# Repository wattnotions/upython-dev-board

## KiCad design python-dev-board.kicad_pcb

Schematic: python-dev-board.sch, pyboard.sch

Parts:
BOOT1: SW_Push; Switches_Push_Switch_506-FSMSM
C1, C2, C3, C4: 12p; C_0603
C5, C6: 2u2; C_0603
C7, C8: 1u; C_0603
C9, C10, C11, C12, C13, C15: 100n; C_0603
C14: 4u7; C_0603
IC1: STM32F405RGT; LQFP64
J3: USB_OTG; USB_Micro-B_Molex-105017-0001
LED1: WS2812B
NRST1: SW_Push; Switches_Push_Switch_506-FSMSM
R2: 1k; R_0603
R3: 10M; R_0603
R4, R5, R6: 100k; R_0603
R7, R8: 15R; R_0603
R9, R10: 4.7k; R_0603
R11, R12: 10K; R_0603
SW1: SW_Push; Switches_Push_Switch_506-FSMSM
Y1: 8MHz; QC5CA8_8mhz_oscillator
Y2: 32.768KHz; ABS06-32.768KHZ_smd_crystal

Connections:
+3V3: BOOT1.2, C8.1, C9.1, C10.1, C11.1, C12.1, C13.1, C14.1, IC1.1 (VBAT), IC1.2 (PC13), IC1.13 (VDDA), IC1.19 (VDD), IC1.32 (VDD), IC1.48 (VDD), IC1.64 (VDD), LED1.1 (VCC), R9.1, R10.1, R11.1; also elsewhere on the board
+BATT: C7.1; also elsewhere on the board
/BOOT0: BOOT1.1, IC1.60 (BOOT0), R4.1
/FS_DM: IC1.44 (PA11), R8.1
/FS_DP: IC1.45 (PA12), R7.1
/FS_USB_ID: IC1.43 (PA10), J3.4 (ID)
/FS_VUSB: IC1.42 (PA9), J3.1 (VBUS)
/GPS_HSD_SW: IC1.9 (PC1)
/GPS_I2C_SCK: IC1.58 (PB6), R10.2
/GPS_I2C_SDA: IC1.59 (PB7), R9.2
/GPS_TX: IC1.30 (PB11), R5.1
/GSM_HSD_SW: IC1.10 (PC2)
/GSM_PWRKEY: IC1.8 (PC0)
/GSM_RX: IC1.29 (PB10)
/INA219_HSD_SW: IC1.26 (PB0)
/INST1_HSD_SW: IC1.25 (PC5)
/INST1_TTL_RX: IC1.14 (PA0)
/INST1_TTL_TX: IC1.15 (PA1)
/INST2_HSD_SW: IC1.24 (PC4)
/INST2_TTL_RX: IC1.16 (PA2)
/INST2_TTL_TX: IC1.17 (PA3)
/INST3_HSD_SW: IC1.11 (PC3)
/INST3_TTL_RX: IC1.37 (PC6)
/INST3_TTL_TX: IC1.38 (PC7)
/IO_PA4: IC1.20 (PA4)
/IO_PA5: IC1.21 (PA5)
/IO_PA6: IC1.22 (PA6)
/IO_PA7: IC1.23 (PA7), LED1.4 (DIN)
/IO_PA14: IC1.49 (PA14)
/IO_PA15: IC1.50 (PA15)
/IO_PB1: IC1.27 (PB1)
/IO_PB2: IC1.28 (PB2), R2.1
/IO_PB3: IC1.55 (PB3)
/IO_PB4: IC1.56 (PB4)
/IO_PB9: IC1.62 (PB9)
/IO_PB12: IC1.33 (PB12)
/IO_PB13: IC1.34 (PB13)
/IO_PB14: IC1.35 (PB14)
/IO_PB15: IC1.36 (PB15)
/LEDR1: IC1.41 (PA8)
/MMA_AVDD: IC1.57 (PB5), R6.1
/N$1: C5.2, IC1.47 (VCAP_2)
/N$2: C6.2, IC1.31 (VCAP_1)
/N$5: C4.1, IC1.3 (PC14), Y2.2
/N$6: C3.1, IC1.4 (PC15), Y2.1
/N$9: C1.1, IC1.6 (PH1), Y1.1
/N$10: C2.1, IC1.5 (PH0), Y1.2
/NRST: C15.1, IC1.7 (NRST), NRST1.2, R11.2
/SDIO_CK: IC1.53 (PC12)
/SDIO_CMD: IC1.54 (PD2)
/SDIO_D0: IC1.39 (PC8)
/SDIO_D1: IC1.40 (PC9)
/SDIO_D2: IC1.51 (PC10)
/SDIO_D3: IC1.52 (PC11), R3.1
/SD_CARD_HSD_SW: IC1.61 (PB8)
/USR_SW: IC1.46 (PA13), R12.2
GND: C1.2, C2.2, C3.2, C4.2, C5.1, C6.1, C7.2, C8.2, C9.2, C10.2, C11.2, C12.2, C13.2, C14.2, C15.2, IC1.12 (VSSA), IC1.18 (VSS), IC1.63 (VSS), J3.5 (GND), LED1.3 (GND), NRST1.1, R2.2, R3.2, R4.2, R5.2, R6.2, SW1.1; also elsewhere on the board
unnamed: J3.2 (D-), R8.2
unnamed: J3.3 (D+), R7.2
unnamed: R12.1, SW1.2

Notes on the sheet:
DFU boot
TX(4)
RX(4)
TX(2)
RX(2)
TX(6)
RX(6)
I2C(1) - SCL
I2C(1) - SDA
TX(3)
RX(3)

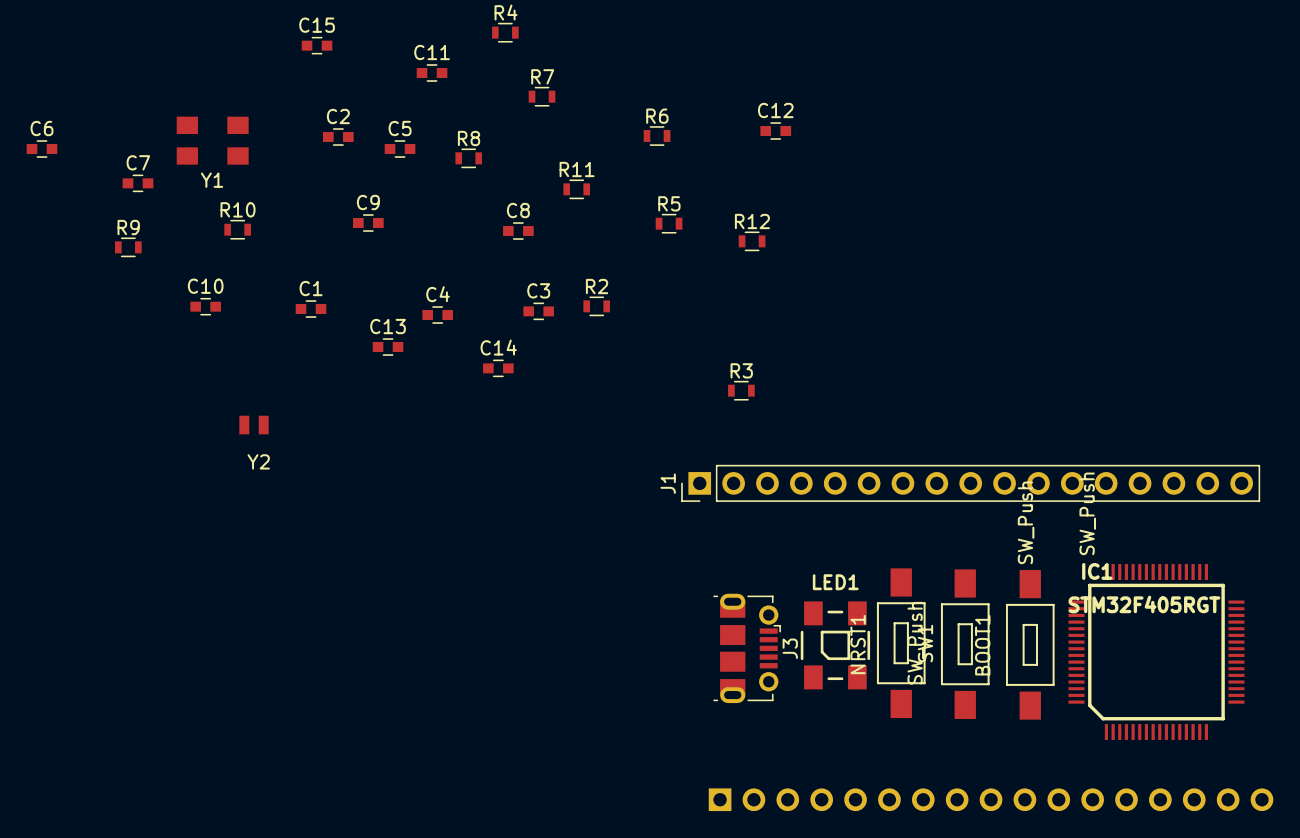
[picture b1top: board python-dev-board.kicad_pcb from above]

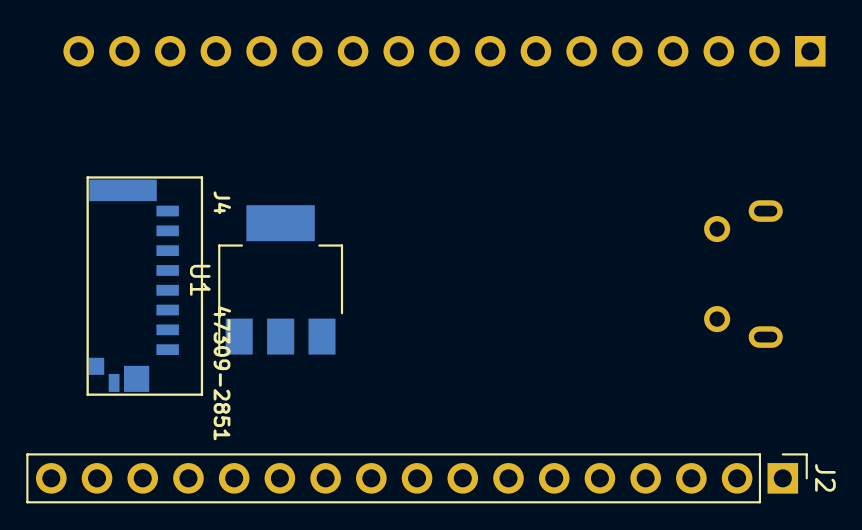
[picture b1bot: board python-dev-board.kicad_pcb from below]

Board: 2 copper layers, 38 parts (3 on the bottom side), 26 nets, no tracks yet.

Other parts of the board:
J1, J2: Conn_01x17; Pin_Header_Straight_1x17_Pitch2.54mm
J4: 47309-2851; molex_sd_47309-2851
U1: LM1117-3.3; SOT-223-3Lead_TabPin2

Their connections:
+3V3: U1.2; also elsewhere on the board
+BATT: U1.3; also elsewhere on the board
GND: J4.G1, J4.G2, U1.1; also elsewhere on the board

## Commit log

2018-07-27 added pin headers to schematic
2018-07-27 shortened pin names on schematic
2018-07-27 connected gpio to pin header
